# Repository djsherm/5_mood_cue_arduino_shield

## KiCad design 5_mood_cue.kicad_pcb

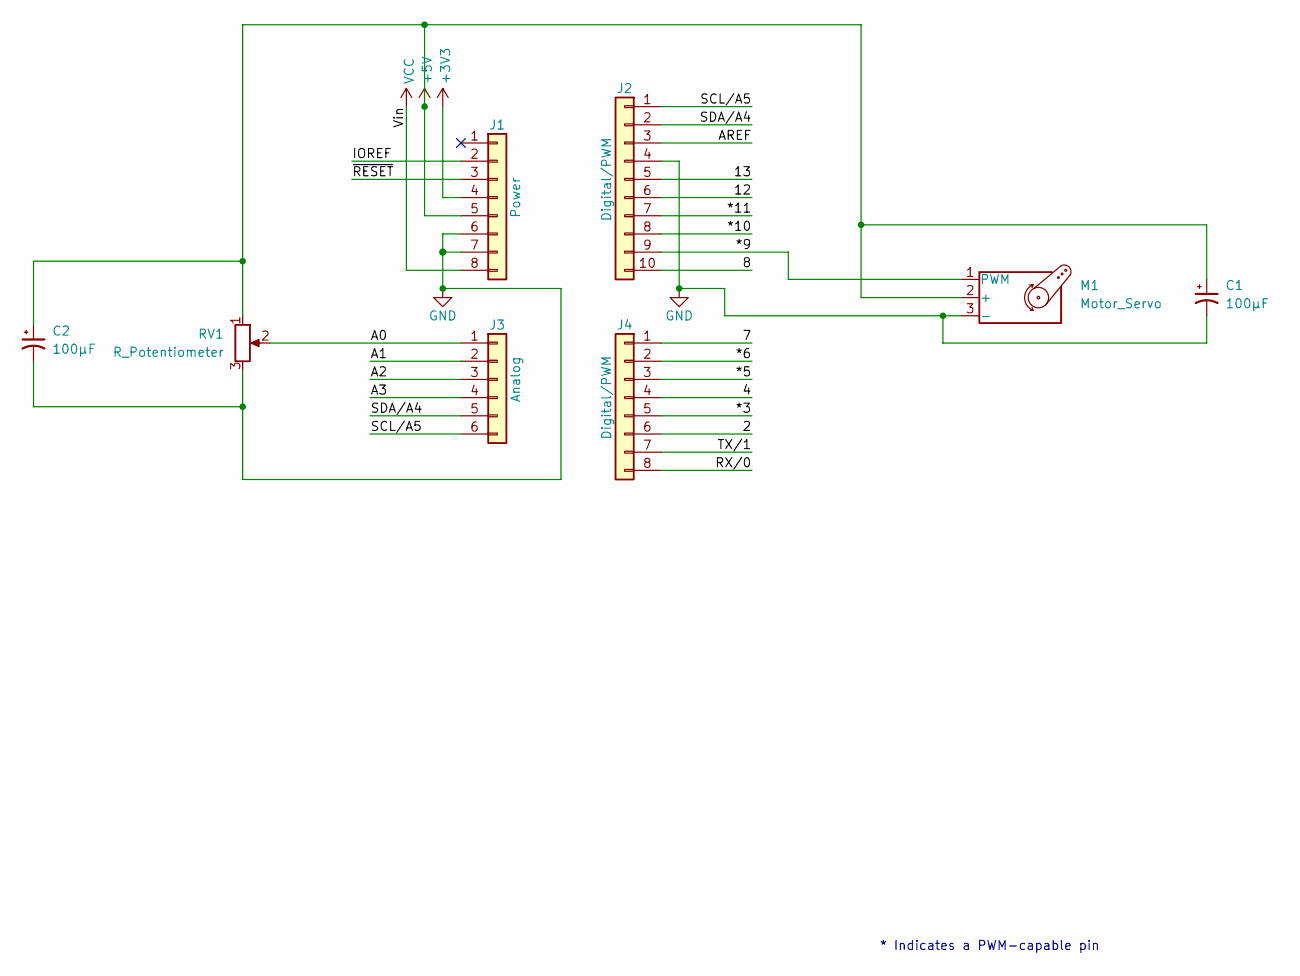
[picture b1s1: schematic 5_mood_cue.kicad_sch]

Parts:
C1, C2: 100μF; CP_Radial_D8.0mm_P5.00mm
J1: Power; PinSocket_1x08_P2.54mm_Vertical
J2: Digital/PWM; PinSocket_1x10_P2.54mm_Vertical
J3: Analog; PinSocket_1x06_P2.54mm_Vertical
J4: Digital/PWM; PinSocket_1x08_P2.54mm_Vertical
M1: Motor_Servo; PinHeader_1x03_P1.27mm_Vertical
RV1: R_Potentiometer; Potentiometer_ACP_CA9-V10_Vertical

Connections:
+3V3: J1.4
+5V: C1.1, C2.1, J1.5, M1.2 (+), RV1.1
/2: J4.6
/4: J4.4
/7: J4.1
/8: J2.10
/12: J2.6
/13: J2.5
/*3: J4.5
/*5: J4.3
/*6: J4.2
/*9: J2.9, M1.1 (PWM)
/*10: J2.8
/*11: J2.7
/A0: J3.1, RV1.2
/A1: J3.2
/A2: J3.3
/A3: J3.4
/AREF: J2.3
/IOREF: J1.2
/RX/0: J4.8
/SCL/A5: J2.1, J3.6
/SDA/A4: J2.2, J3.5
/TX/1: J4.7
/~RESET: J1.3
GND: C1.2, C2.2, J1.6, J1.7, J2.4, M1.3 (-), RV1.3
VCC: J1.8

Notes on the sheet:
* Indicates a PWM-capable pin

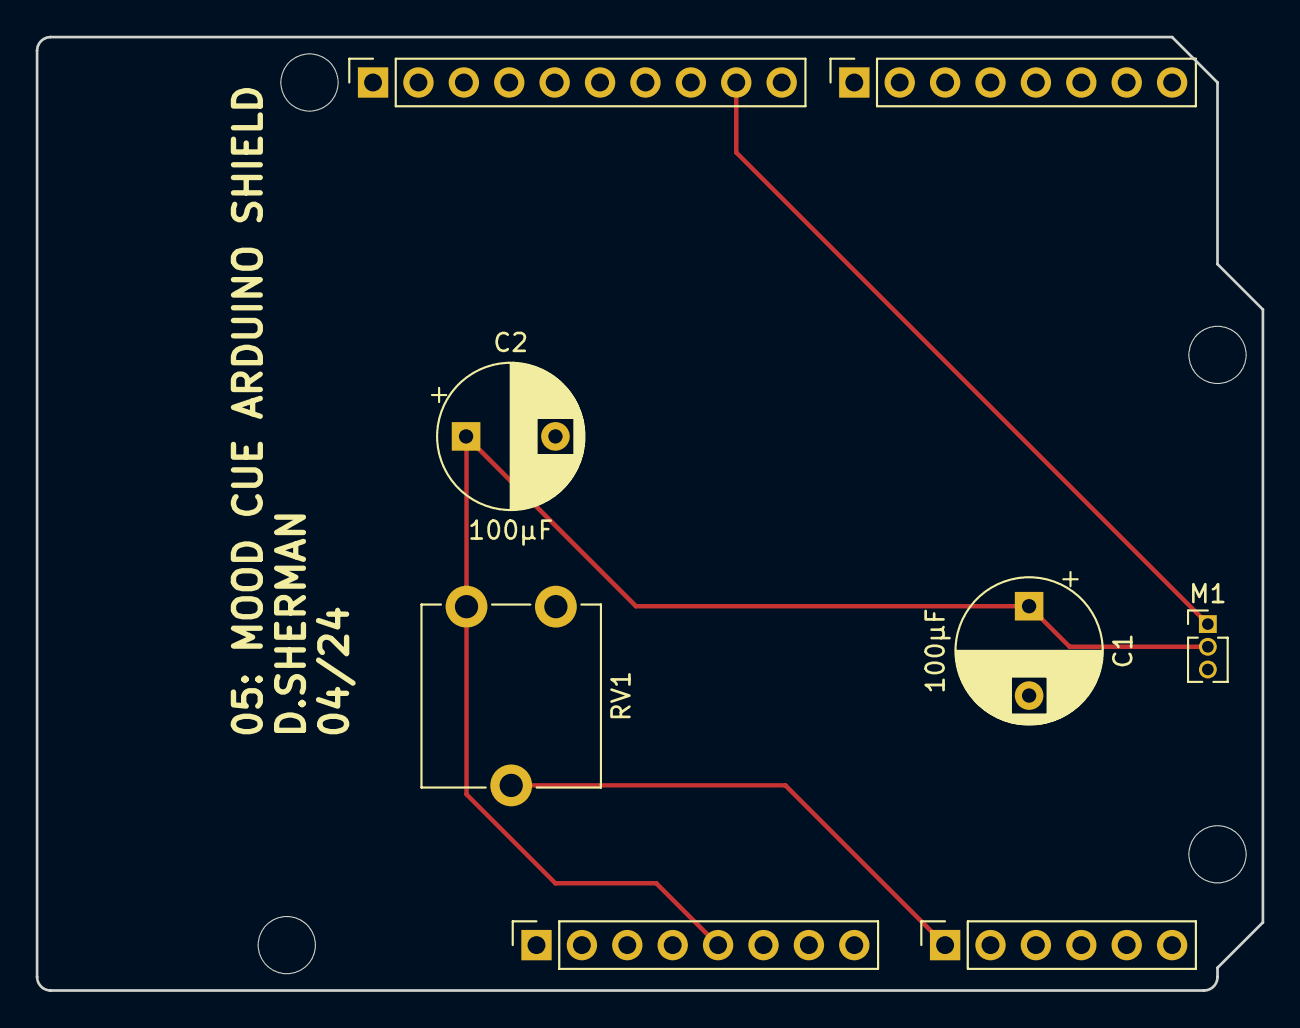
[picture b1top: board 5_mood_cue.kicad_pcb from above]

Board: 2 copper layers, 68.6 x 53.3 mm, 12 parts (0 on the bottom side), 6 nets.

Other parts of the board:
MH1, MH2, MH3, MH4: MountingHole_3.2mm

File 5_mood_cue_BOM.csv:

"Reference","Value","Datasheet","Footprint","Qty","DNP"
"C1.C2","100μF","~","Capacitor_THT:CP_Radial_D8.0mm_P5.00mm","2",""
"J1","Power","","Connector_PinSocket_2.54mm:PinSocket_1x08_P2.54mm_Vertical","1",""
"J2.J4","Digital/PWM","","-- mixed values --","2",""
"J3","Analog","~","Connector_PinSocket_2.54mm:PinSocket_1x06_P2.54mm_Vertical","1",""
"M1","Motor_Servo","http://forums.parallax.com/uploads/attachments/46831/74481.png","Connector_PinHeader_1.27mm:PinHeader_1x03_P1.27mm_Vertical","1",""
"RV1","R_Potentiometer","~","Potentiometer_THT:Potentiometer_ACP_CA9-V10_Vertical","1",""
